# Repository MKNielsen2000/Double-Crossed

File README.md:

# Double-Crossed
2 x Vactrol Crossfader in Eurorack format

Two delicious vactrol based crossfaders inspired by Mark Verbos and Don Buchla. 

The top crossfader (crossfader A) is DC coupled and thus optimal for crossfading CV signales to create complex cv signals. 

The bottom crossfader (crossfader B) is AC coupled and thus optimal for audio signals, eg. crossfading between two waveforms, sequences or samples. 

If a signal is patched into the cv input of crossfader A, but nothing is patched into the cv input of crossfader B, the signal at crossfader A's input is automatically sent to crossfader B's cv input. 

###Status
* Prototypes sent to fab

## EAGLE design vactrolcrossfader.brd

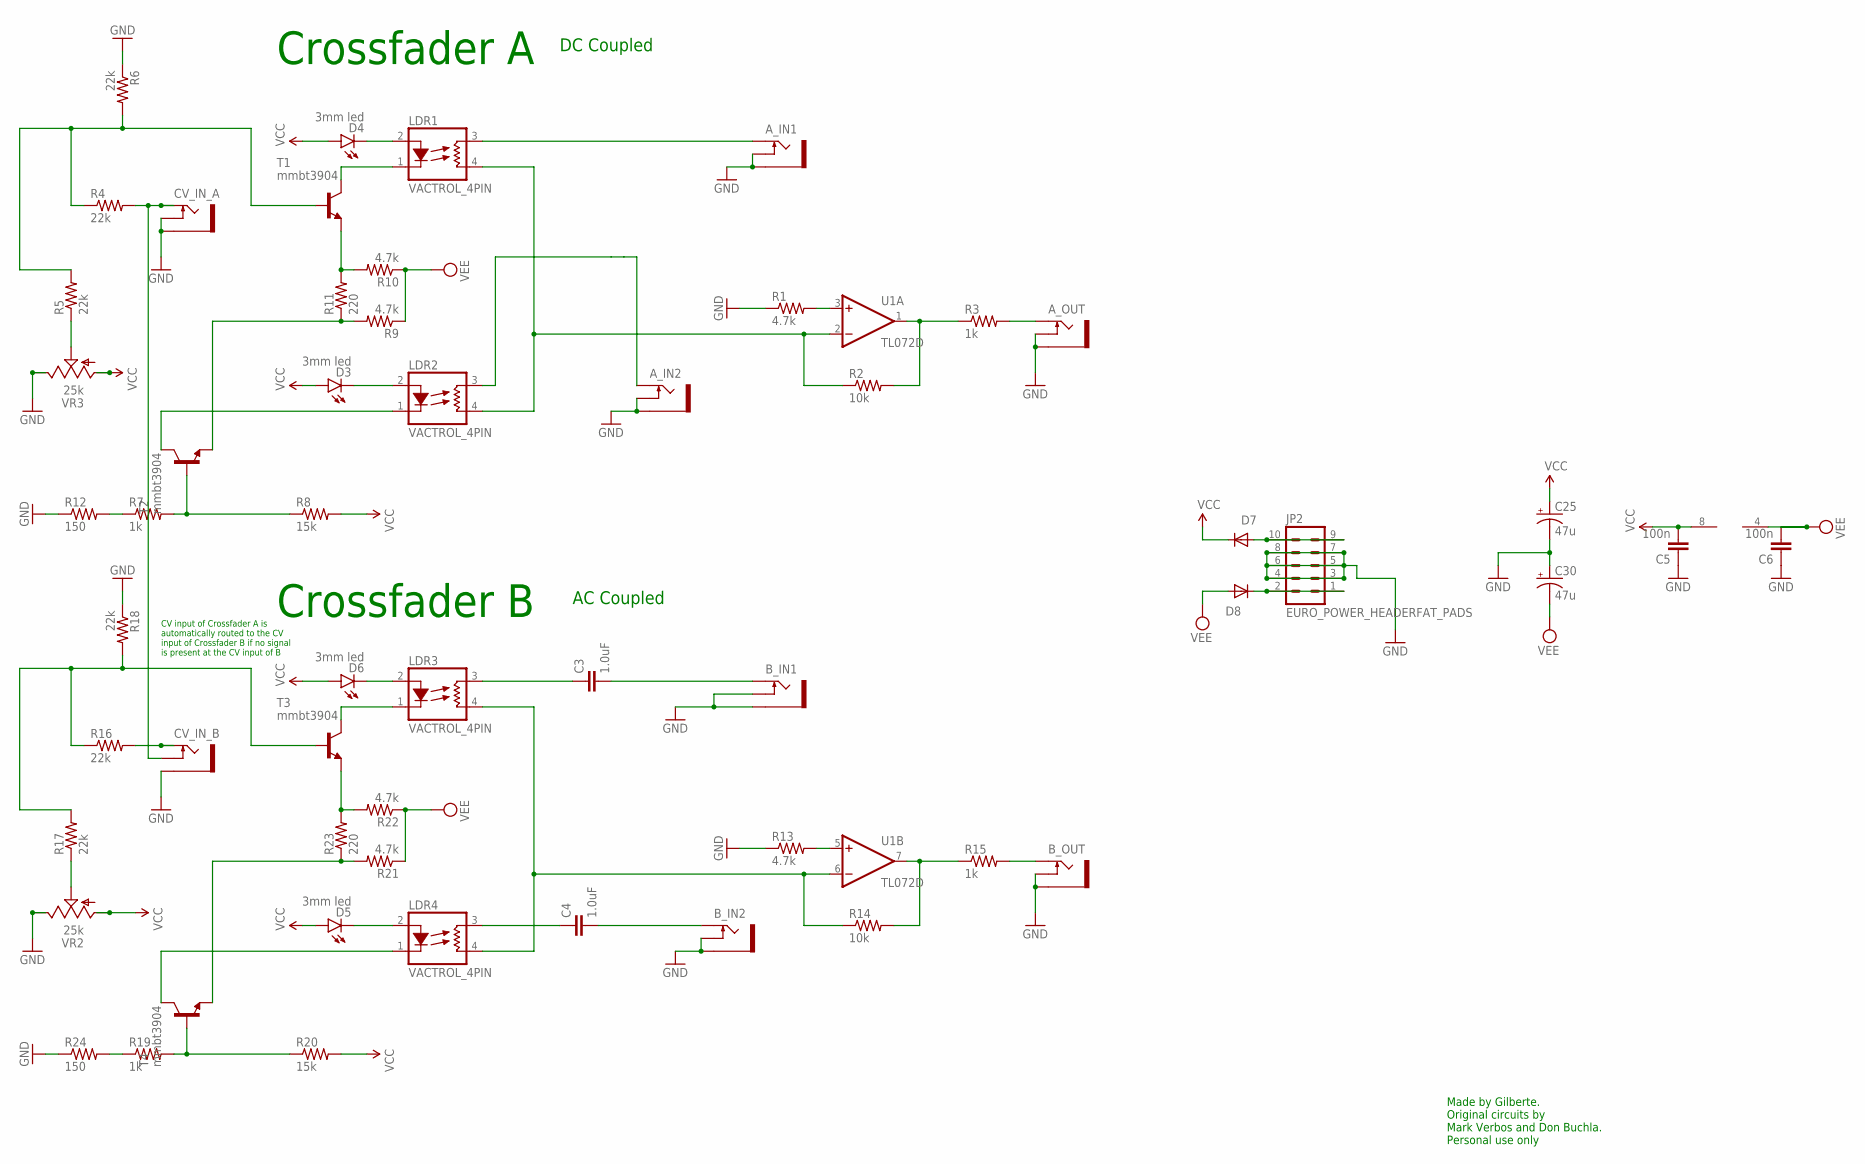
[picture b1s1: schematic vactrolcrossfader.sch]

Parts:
A_IN1, A_IN2: THONKICONNNEW; WQP-PJ301M-12_JACK
A_OUT: THONKICONNNEW; WQP-PJ301M-12_JACK
B_IN1, B_IN2: THONKICONNNEW; WQP-PJ301M-12_JACK
B_OUT: THONKICONNNEW; WQP-PJ301M-12_JACK
C3, C4: 1.0uF; 0805
C5, C6: 100n; 0805
C25, C30: 47u; PANASONIC_D
CV_IN_A: THONKICONNNEW; WQP-PJ301M-12_JACK
CV_IN_B: THONKICONNNEW; WQP-PJ301M-12_JACK
D3, D4, D5, D6: 3mm led; LED3MM
D7, D8: 1N5819HW; SOD123
JP2: EURO_POWER_HEADERFAT_PADS; EURO_PWR_HEADER_FAT
LDR1, LDR2, LDR3, LDR4: VACTROL_4PIN; VACTROL_4PIN_VTL5C
R1, R9, R10, R13, R21, R22: 4.7k; 1206
R2, R14: 10k; 1206
R3, R7, R15, R19: 1k; 1206
R4, R5, R6, R16, R17, R18: 22k; 1206
R8, R20: 15k; 1206
R11, R23: 220; 1206
R12, R24: 150; 1206
T1, T2, T3, T4: mmbt3904; SOT23-BEC
U1: TL072D; SO08
VR2, VR3: 25k; 9MM_SNAP-IN_POT

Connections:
GND: A_IN1.P$2_SWITCH (SWITCH), A_IN1.P$3_SLEEVE (SLEEVE), A_IN2.P$2_SWITCH (SWITCH), A_IN2.P$3_SLEEVE (SLEEVE), A_OUT.P$2_SWITCH (SWITCH), A_OUT.P$3_SLEEVE (SLEEVE), B_IN1.P$2_SWITCH (SWITCH), B_IN1.P$3_SLEEVE (SLEEVE), B_IN2.P$2_SWITCH (SWITCH), B_IN2.P$3_SLEEVE (SLEEVE), B_OUT.P$2_SWITCH (SWITCH), B_OUT.P$3_SLEEVE (SLEEVE), C5.1, C6.1, C25.-, C30.+, CV_IN_A.P$2_SWITCH (SWITCH), CV_IN_A.P$3_SLEEVE (SLEEVE), CV_IN_B.P$3_SLEEVE (SLEEVE), JP2.3, JP2.4, JP2.5, JP2.6, JP2.7, JP2.8, R1.1, R6.1, R12.1, R13.1, R18.1, R24.1, VR2.3 (E), VR3.3 (E)
unnamed: A_IN2.P$1_TIP (TIP), LDR2.3 (RES1)
unnamed: LDR1.4 (RES2), LDR2.4 (RES2), R2.1, U1.2 (-IN)
unnamed: R1.2, U1.3 (+IN)
unnamed: D3.K (C), LDR2.2 (LED+)
unnamed: LDR2.1 (LED-), T2.C
unnamed: R2.2, R3.1, U1.1 (OUT)
unnamed: A_OUT.P$1_TIP (TIP), R3.2
unnamed: LDR1.1 (LED-), T1.C
unnamed: CV_IN_A.P$1_TIP (TIP), CV_IN_B.P$2_SWITCH (SWITCH), R4.2
unnamed: R4.1, R5.2, R6.2, T1.B
unnamed: R5.1, VR3.2 (S)
unnamed: A_IN1.P$1_TIP (TIP), LDR1.3 (RES1)
unnamed: R7.2, R8.1, T2.B
unnamed: R9.2, R11.1, T2.E
unnamed: R10.2, R11.2, T1.E
unnamed: R7.1, R12.2
unnamed: D4.K (C), LDR1.2 (LED+)
unnamed: LDR3.4 (RES2), LDR4.4 (RES2), R14.1, U1.6 (-IN)
unnamed: R13.2, U1.5 (+IN)
unnamed: R14.2, R15.1, U1.7 (OUT)
unnamed: B_OUT.P$1_TIP (TIP), R15.2
unnamed: D5.K (C), LDR4.2 (LED+)
unnamed: LDR3.1 (LED-), T3.C
unnamed: CV_IN_B.P$1_TIP (TIP), R16.2
unnamed: R16.1, R17.2, R18.2, T3.B
unnamed: R17.1, VR2.2 (S)
unnamed: R19.2, R20.1, T4.B
unnamed: R21.2, R23.1, T4.E
unnamed: R22.2, R23.2, T3.E
unnamed: LDR4.1 (LED-), T4.C
unnamed: R19.1, R24.2
unnamed: D6.K (C), LDR3.2 (LED+)
unnamed: B_IN2.P$1_TIP (TIP), C4.2
unnamed: B_IN1.P$1_TIP (TIP), C3.2
unnamed: C3.1, LDR3.3 (RES1)
unnamed: C4.1, LDR4.3 (RES1)
unnamed: D8.C, JP2.1, JP2.2
unnamed: D7.A, JP2.9, JP2.10
VCC: C5.2, C25.+, D3.A, D4.A, D5.A, D6.A, D7.C, R8.2, R20.2, U1.8 (V+), VR2.1 (A), VR3.1 (A)
VEE: C6.2, C30.-, D8.A, R9.1, R10.1, R21.1, R22.1, U1.4 (V-)

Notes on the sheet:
Made by Gilberte. Original circuits by Mark Verbos and Don Buchla. Personal use only
Crossfader A
Crossfader B
DC Coupled
AC Coupled
CV input of Crossfader A is automatically routed to the CV input of Crossfader B if no signal is present at the CV input of B

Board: 2 copper layers, 56 parts (37 on the bottom side), 41 nets, no tracks yet.

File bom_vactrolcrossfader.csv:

"Part";"Value";"Device";"Package";"Description";"PROD_ID";
"A_IN1";"THONKICONNNEW";"THONKICONNNEW";"WQP-PJ301M-12_JACK";"3.5mm socket for Eurorack modular synths";"";
"A_IN2";"THONKICONNNEW";"THONKICONNNEW";"WQP-PJ301M-12_JACK";"3.5mm socket for Eurorack modular synths";"";
"A_OUT";"THONKICONNNEW";"THONKICONNNEW";"WQP-PJ301M-12_JACK";"3.5mm socket for Eurorack modular synths";"";
"B_IN1";"THONKICONNNEW";"THONKICONNNEW";"WQP-PJ301M-12_JACK";"3.5mm socket for Eurorack modular synths";"";
"B_IN2";"THONKICONNNEW";"THONKICONNNEW";"WQP-PJ301M-12_JACK";"3.5mm socket for Eurorack modular synths";"";
"B_OUT";"THONKICONNNEW";"THONKICONNNEW";"WQP-PJ301M-12_JACK";"3.5mm socket for Eurorack modular synths";"";
"C3";"1.0uF";"CAP0805";"0805";"Capacitor";"";
"C4";"1.0uF";"CAP0805";"0805";"Capacitor";"";
"C5";"100n";"CAP0805";"0805";"Capacitor";"";
"C6";"100n";"CAP0805";"0805";"Capacitor";"";
"C25";"47u";"CPOL-USD";"PANASONIC_D";"POLARIZED CAPACITOR, American symbol";"";
"C30";"47u";"CPOL-USD";"PANASONIC_D";"POLARIZED CAPACITOR, American symbol";"";
"CV_IN_A";"THONKICONNNEW";"THONKICONNNEW";"WQP-PJ301M-12_JACK";"3.5mm socket for Eurorack modular synths";"";
"CV_IN_B";"THONKICONNNEW";"THONKICONNNEW";"WQP-PJ301M-12_JACK";"3.5mm socket for Eurorack modular synths";"";
"D3";"";"LED3MM";"LED3MM";"LEDs";"DIO-08794";
"D4";"";"LED3MM";"LED3MM";"LEDs";"DIO-08794";
"D5";"";"LED3MM";"LED3MM";"LEDs";"DIO-08794";
"D6";"";"LED3MM";"LED3MM";"LEDs";"DIO-08794";
"D7";"1N5819HW";"DIODE-SOD123";"SOD123";"DIODE";"";
"D8";"1N5819HW";"DIODE-SOD123";"SOD123";"DIODE";"";
"JP2";"EURO_POWER_HEADERFAT_PADS";"EURO_POWER_HEADERFAT_PADS";"EURO_PWR_HEADER_FAT";"Power Header";"";
"LDR1";"VACTROL_4PIN";"VACTROL_4PIN";"VACTROL_4PIN_VTL5C";"4 Pin Vactrol Resistive Photocoupler";"";
"LDR2";"VACTROL_4PIN";"VACTROL_4PIN";"VACTROL_4PIN_VTL5C";"4 Pin Vactrol Resistive Photocoupler";"";
"LDR3";"VACTROL_4PIN";"VACTROL_4PIN";"VACTROL_4PIN_VTL5C";"4 Pin Vactrol Resistive Photocoupler";"";
"LDR4";"VACTROL_4PIN";"VACTROL_4PIN";"VACTROL_4PIN_VTL5C";"4 Pin Vactrol Resistive Photocoupler";"";
"R1";"4.7k";"RESISTOR1206";"1206";"Resistor";"";
"R2";"1k";"RESISTOR1206";"1206";"Resistor";"";
"R3";"1k";"RESISTOR1206";"1206";"Resistor";"";
"R4";"22k";"RESISTOR1206";"1206";"Resistor";"";
"R5";"22k";"RESISTOR1206";"1206";"Resistor";"";
"R6";"22k";"RESISTOR1206";"1206";"Resistor";"";
"R7";"1k";"RESISTOR1206";"1206";"Resistor";"";
"R8";"15k";"RESISTOR1206";"1206";"Resistor";"";
"R9";"4.7k";"RESISTOR1206";"1206";"Resistor";"";
"R10";"4.7k";"RESISTOR1206";"1206";"Resistor";"";
"R11";"220";"RESISTOR1206";"1206";"Resistor";"";
"R12";"150";"RESISTOR1206";"1206";"Resistor";"";
"R13";"4.7k";"RESISTOR1206";"1206";"Resistor";"";
"R14";"1k";"RESISTOR1206";"1206";"Resistor";"";
"R15";"1k";"RESISTOR1206";"1206";"Resistor";"";
"R16";"22k";"RESISTOR1206";"1206";"Resistor";"";
"R17";"22k";"RESISTOR1206";"1206";"Resistor";"";
"R18";"22k";"RESISTOR1206";"1206";"Resistor";"";
"R19";"1k";"RESISTOR1206";"1206";"Resistor";"";
"R20";"15k";"RESISTOR1206";"1206";"Resistor";"";
"R21";"4.7k";"RESISTOR1206";"1206";"Resistor";"";
"R22";"4.7k";"RESISTOR1206";"1206";"Resistor";"";
"R23";"220";"RESISTOR1206";"1206";"Resistor";"";
"R24";"150";"RESISTOR1206";"1206";"Resistor";"";
"T1";"";"MMBT3904LT1-NPN-SOT23-BEC";"SOT23-BEC";"NPN Transistror";"";
"T2";"";"MMBT3904LT1-NPN-SOT23-BEC";"SOT23-BEC";"NPN Transistror";"";
"T3";"";"MMBT3904LT1-NPN-SOT23-BEC";"SOT23-BEC";"NPN Transistror";"";
"T4";"";"MMBT3904LT1-NPN-SOT23-BEC";"SOT23-BEC";"NPN Transistror";"";
"U1";"TL072_SMD";"TL072_SMD";"SO08";"Generic Dual Op Amp";"";
"VR1";"20k";"BOURNS_3362P_TRIMMERP";"BOURNS_3362P_TRIMMER";"3362 Series";"";
"VR4";"20k";"BOURNS_3362P_TRIMMERP";"BOURNS_3362P_TRIMMER";"3362 Series";"";

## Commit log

2016-07-17 first commit
    first commit
2016-07-17 Added switch to CV inputs
2016-07-18 First board layout done
2016-07-18 ready update
2016-07-18 board done
2016-07-18 OSH images added
2016-07-18 updated board to v 1.1: Better silk screen legibility on smd components, trimmers moved to backside
2016-07-20 Prototype board updated and sent to fab
2016-07-20 rmu2
2016-07-20 rmu3
2016-07-20 rmu4
2016-07-20 Moved power caps to make room for trimmers
2016-07-25 front panel+bom added
    front panel+bom added
2016-08-14 v1.2 first commit

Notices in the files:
parts and their libraries:
SparkFun-Passives: Licensing: Creative Commons ShareAlike 4.0 International - https://creativecommons.org/licenses/by-sa/4.0
